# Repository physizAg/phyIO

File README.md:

# What is PhyIO

PhyIO is an IoT development board with ARM cortex-M4 MCU and CC3100 WiFi chipset. It is designed for tinkerers who need high processing and good wireless connectivity for their IoT projects.

Multiple onboard interfaces like I2C, UART, SPI, and RS485 make it easy to experiment with various sensors and actuators. With its extensive features and rugged design, there are endless possibilities.

# Features

1) Onboard Cortex-M4 based STM32 MCU
2) The PhyIO's wireless chip supports 802.11ac/a/b/g/n WiFI
3) Regulates 12V input to 5V and 3.3V
4) Supports transistor-based switching for driving loads
5) Supports I2C, SPI, UART, and RS485 interface
6) Onboard power indicator LED
7) Flexibility to select specific voltage levels amongst multiple voltage levels for interfaces

## Specs

<li>12V input supply</li>
<li>1 MB Flash memory</li>
<li>256Kb RAM</li>
<li>8 I2C ports</li>
<li>4 SPI ports</li>
<li>1 UART port</li>
<li>RS485 port</li>
<li>10 GPIO ports</li>
<li>4 12-bit ADC channels</li>

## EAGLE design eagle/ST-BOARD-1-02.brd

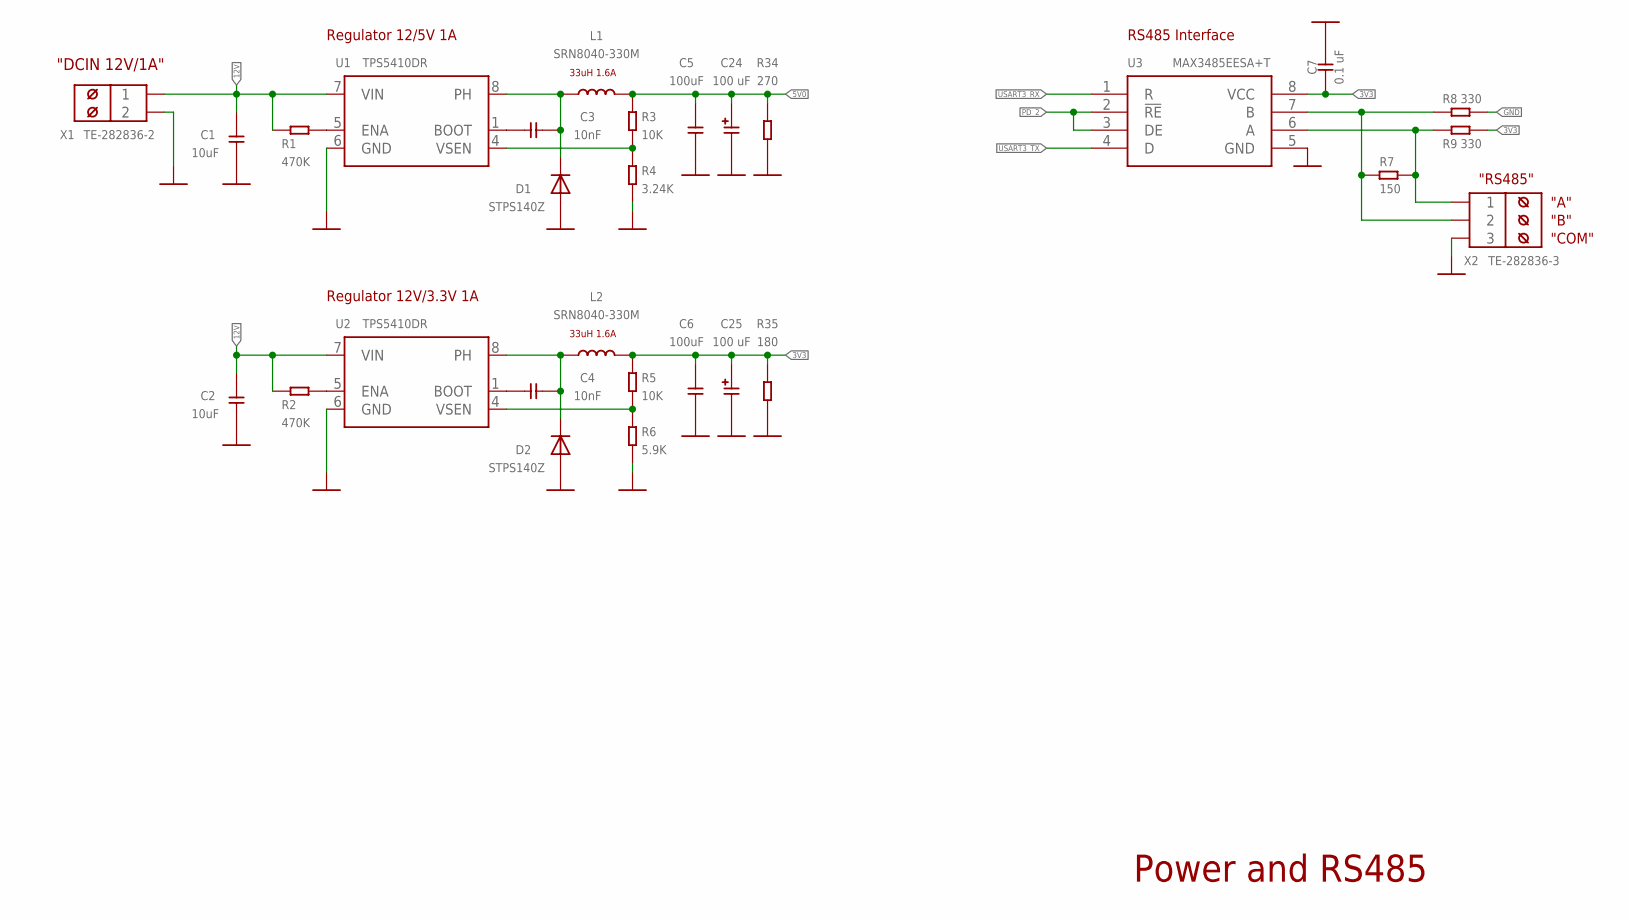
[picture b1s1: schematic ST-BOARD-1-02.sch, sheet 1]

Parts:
C1, C2: 10uF; C1206
C3, C4: 10nF; C0603
C5, C6: 100uF; C1206
C7: 0.1 uF; C0603
C24, C25: 100 uF; CT7343
D1, D2: STPS140Z; SOD-123
L1, L2: SRN8040-330M; SRN8040
R1, R2: 470K; R0603
R3, R5: 10K; R0603
R4: 3.24K; R0603
R6: 5.9K; R0603
R7: 150; R0805
R8, R9: 330; R0603
R34: 270; R1206
R35: 180; R1206
U1, U2: TPS5410DR; SOIC8
U3: MAX3485EESA+T; SOIC8
X1: TE-282836-2; W237-102
X2: TE-282836-3; W237-103

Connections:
3V3: C6.2, C7.1, C25.+, L2.2, R5.2, R9.1, R35.2, U3.8 (VCC); also elsewhere on the board
5V0: C5.2, C24.+, L1.2, R3.2, R34.2; also elsewhere on the board
12V: C1.1, C2.1, R1.2, R2.2, U1.7 (VIN), U2.7 (VIN), X1.1; also elsewhere on the board
A: R7.2, R9.2, U3.6 (A), X2.1
B: R7.1, R8.2, U3.7 (B), X2.2
GND: C1.2, C2.2, C5.1, C6.1, C7.2, C24.-, C25.-, D1.+, D2.+, R4.1, R6.1, R8.1, R34.1, R35.1, U1.6 (GND), U2.6 (GND), U3.5 (GND), X1.2, X2.3; also elsewhere on the board
LM_SW1: C3.2, D1.-, L1.1, U1.8 (PH)
LM_SW3: C4.2, D2.-, L2.1, U2.8 (PH)
unnamed: R3.1, R4.2, U1.4 (VSEN)
unnamed: C3.1, U1.1 (BOOT)
unnamed: R1.1, U1.5 (ENA)
unnamed: R5.1, R6.2, U2.4 (VSEN)
unnamed: C4.1, U2.1 (BOOT)
unnamed: R2.1, U2.5 (ENA)
PD_2: U3.2 (!RE), U3.3 (DE); also elsewhere on the board
USART3_RX: U3.1 (R); also elsewhere on the board
USART3_TX: U3.4 (D); also elsewhere on the board

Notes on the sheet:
"DCIN 12V/1A"
Regulator 12/5V 1A
33uH 1.6A
Regulator 12V/3.3V 1A
RS485 Interface
"RS485"
"A"
"B"
"COM"
Power and RS485

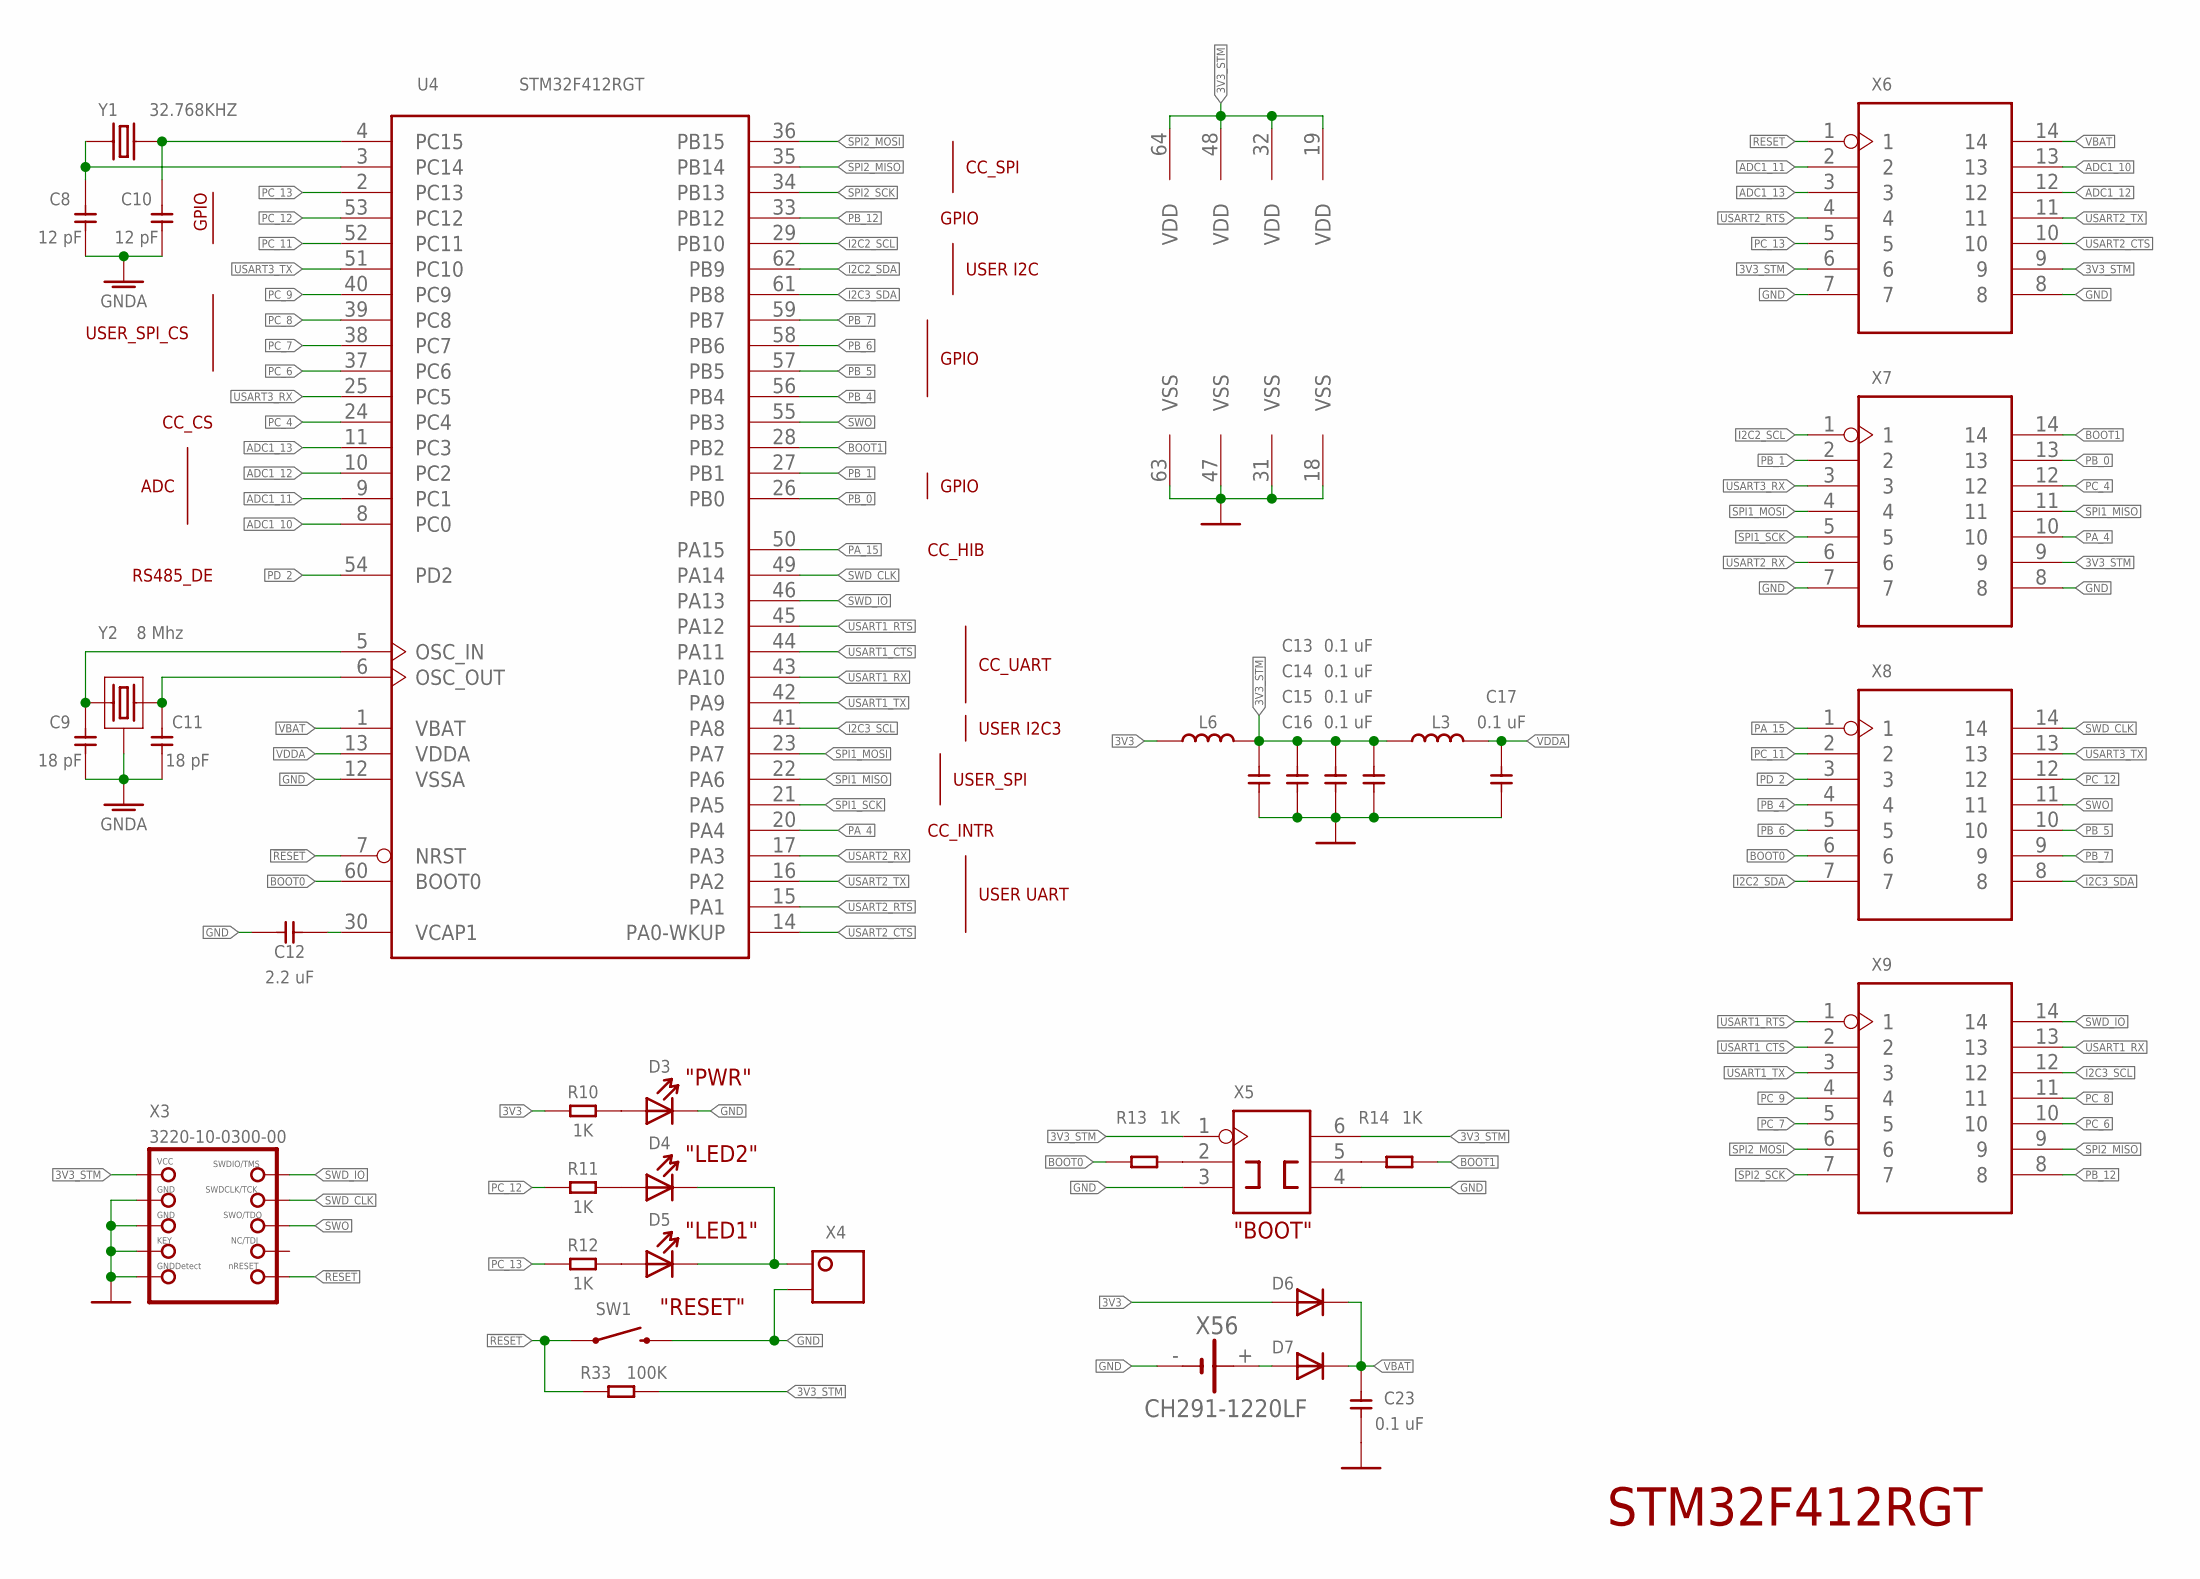
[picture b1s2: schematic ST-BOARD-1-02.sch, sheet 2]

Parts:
C8, C10: 12 pF; C0603
C9, C11: 18 pF; C0603
C12: 2.2 uF; C0603
C13, C14, C15, C16, C17, C23: 0.1 uF; C0603
D3, D4, D5: LED-0603
D6, D7: DIODE_SOD-523; SOD-523
L3, L6: CHIP-INDUCTOR_L0603; L0603
R10, R11, R12, R13, R14: 1K; R0603
R33: 100K; R0603
SW1: TE-1437566-3
U4: STM32F412RGT; LQFP64
X3: 3220-10-0300-00; 2X05_1.27MM_BOX_NOPOSTS
X4: 2p-2.54; H2-2.54
X5: 2x3p-2.54; H2X3-2.54
X6, X7, X8, X9: DIP-HEADER-VERT(2X7P-2.54); H2X7-2.54
X56: CH291-1220LF
Y1: 32.768KHZ; 3.2X1.5; MPN KX-327NHT 32.768 kHz GEYER
Y2: 8 Mhz; IQG5032B

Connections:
3V3: D6.+, L6.1, R10.1; also elsewhere on the board
3V3_STM: C13.1, C14.1, C15.1, C16.1, L3.2, L6.2, R33.1, U4.19 (VDD), U4.32 (VDD), U4.48 (VDD), U4.64 (VDD), X3.1 (VCC), X5.1, X5.6, X6.6, X6.9, X7.9
!RESET: R33.2, SW1.P$1 (1), U4.7 (NRST), X3.10 (NRESET), X6.1
ADC1_10: U4.8 (PC0), X6.13; also elsewhere on the board
ADC1_11: U4.9 (PC1), X6.2; also elsewhere on the board
ADC1_12: U4.10 (PC2), X6.12; also elsewhere on the board
ADC1_13: U4.11 (PC3), X6.3; also elsewhere on the board
BOOT0: R13.1, U4.60 (BOOT0), X8.6
BOOT1: R14.1, U4.28 (PB2), X7.14
GND: C12.2, C13.2, C14.2, C15.2, C16.2, C17.2, C23.2, D3.-, SW1.P$2 (2), U4.12 (VSSA), U4.18 (VSS), U4.31 (VSS), U4.47 (VSS), U4.63 (VSS), X3.3 (GND), X3.5 (GND), X3.7 (KEY), X3.9 (GNDDETECT), X4.2, X5.3, X5.4, X6.7, X6.8, X7.7, X7.8, X56.-; also elsewhere on the board
GNDA: C8.1, C9.1, C10.1, C11.1, Y2.2 (GND), Y2.4 (GND)
I2C2_SCL: U4.29 (PB10), X7.1; also elsewhere on the board
I2C2_SDA: U4.62 (PB9), X8.7; also elsewhere on the board
I2C3_SCL: U4.41 (PA8), X9.12; also elsewhere on the board
I2C3_SDA: U4.61 (PB8), X8.8; also elsewhere on the board
unnamed: C10.2, U4.4 (PC15), Y1.2
unnamed: C8.2, U4.3 (PC14), Y1.1
unnamed: C12.1, U4.30 (VCAP1)
unnamed: C11.2, U4.6 (OSC_OUT), Y2.3 (2)
unnamed: C9.2, U4.5 (OSC_IN), Y2.1
unnamed: D3.+, R10.2
unnamed: D4.+, R11.2
unnamed: D5.+, R12.2
unnamed: D7.+, X56.+
unnamed: R14.2, X5.5
unnamed: R13.2, X5.2
unnamed: D4.-, D5.-, X4.1
PA_4: U4.20 (PA4), X7.10; also elsewhere on the board
PA_15: U4.50 (PA15), X8.1; also elsewhere on the board
PB_0: U4.26 (PB0), X7.13; also elsewhere on the board
PB_1: U4.27 (PB1), X7.2; also elsewhere on the board
PB_4: U4.56 (PB4), X8.4; also elsewhere on the board
PB_5: U4.57 (PB5), X8.10; also elsewhere on the board
PB_6: U4.58 (PB6), X8.5; also elsewhere on the board
PB_7: U4.59 (PB7), X8.9; also elsewhere on the board
PB_12: U4.33 (PB12), X9.8; also elsewhere on the board
PC_4: U4.24 (PC4), X7.12; also elsewhere on the board
PC_6: U4.37 (PC6), X9.10; also elsewhere on the board
PC_7: U4.38 (PC7), X9.5; also elsewhere on the board
PC_8: U4.39 (PC8), X9.11; also elsewhere on the board
PC_9: U4.40 (PC9), X9.4; also elsewhere on the board
PC_11: U4.52 (PC11), X8.2; also elsewhere on the board
PC_12: R11.1, U4.53 (PC12), X8.12; also elsewhere on the board
PC_13: R12.1, U4.2 (PC13), X6.5; also elsewhere on the board
PD_2: U4.54 (PD2), X8.3; also elsewhere on the board
SPI1_MISO: U4.22 (PA6), X7.11; also elsewhere on the board
SPI1_MOSI: U4.23 (PA7), X7.4; also elsewhere on the board
SPI1_SCK: U4.21 (PA5), X7.5; also elsewhere on the board
SPI2_MISO: U4.35 (PB14), X9.9; also elsewhere on the board
SPI2_MOSI: U4.36 (PB15), X9.6; also elsewhere on the board
SPI2_SCK: U4.34 (PB13), X9.7; also elsewhere on the board
SWD_CLK: U4.49 (PA14), X3.4 (SWDCLK), X8.14
SWD_IO: U4.46 (PA13), X3.2 (SWDIO), X9.14
SWO: U4.55 (PB3), X3.6 (SWO), X8.11
USART1_CTS: U4.44 (PA11), X9.2; also elsewhere on the board
USART1_RTS: U4.45 (PA12), X9.1; also elsewhere on the board
USART1_RX: U4.43 (PA10), X9.13; also elsewhere on the board
USART1_TX: U4.42 (PA9), X9.3; also elsewhere on the board
USART2_CTS: U4.14 (PA0-WKUP), X6.10; also elsewhere on the board
USART2_RTS: U4.15 (PA1), X6.4; also elsewhere on the board
USART2_RX: U4.17 (PA3), X7.6; also elsewhere on the board
USART2_TX: U4.16 (PA2), X6.11; also elsewhere on the board
USART3_RX: U4.25 (PC5), X7.3; also elsewhere on the board
USART3_TX: U4.51 (PC10), X8.13; also elsewhere on the board
VBAT: C23.1, D6.-, D7.-, U4.1 (VBAT), X6.14
VDDA: C17.1, L3.1, U4.13 (VDDA)

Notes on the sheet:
STM32F412RGT
"PWR"
"LED2"
"LED1"
"RESET"
USER UART
CC_UART
USER_SPI
USER I2C
USER I2C3
CC_SPI
"BOOT"
RS485_DE
ADC
GPIO
USER_SPI_CS
CC_INTR
CC_HIB
CC_CS

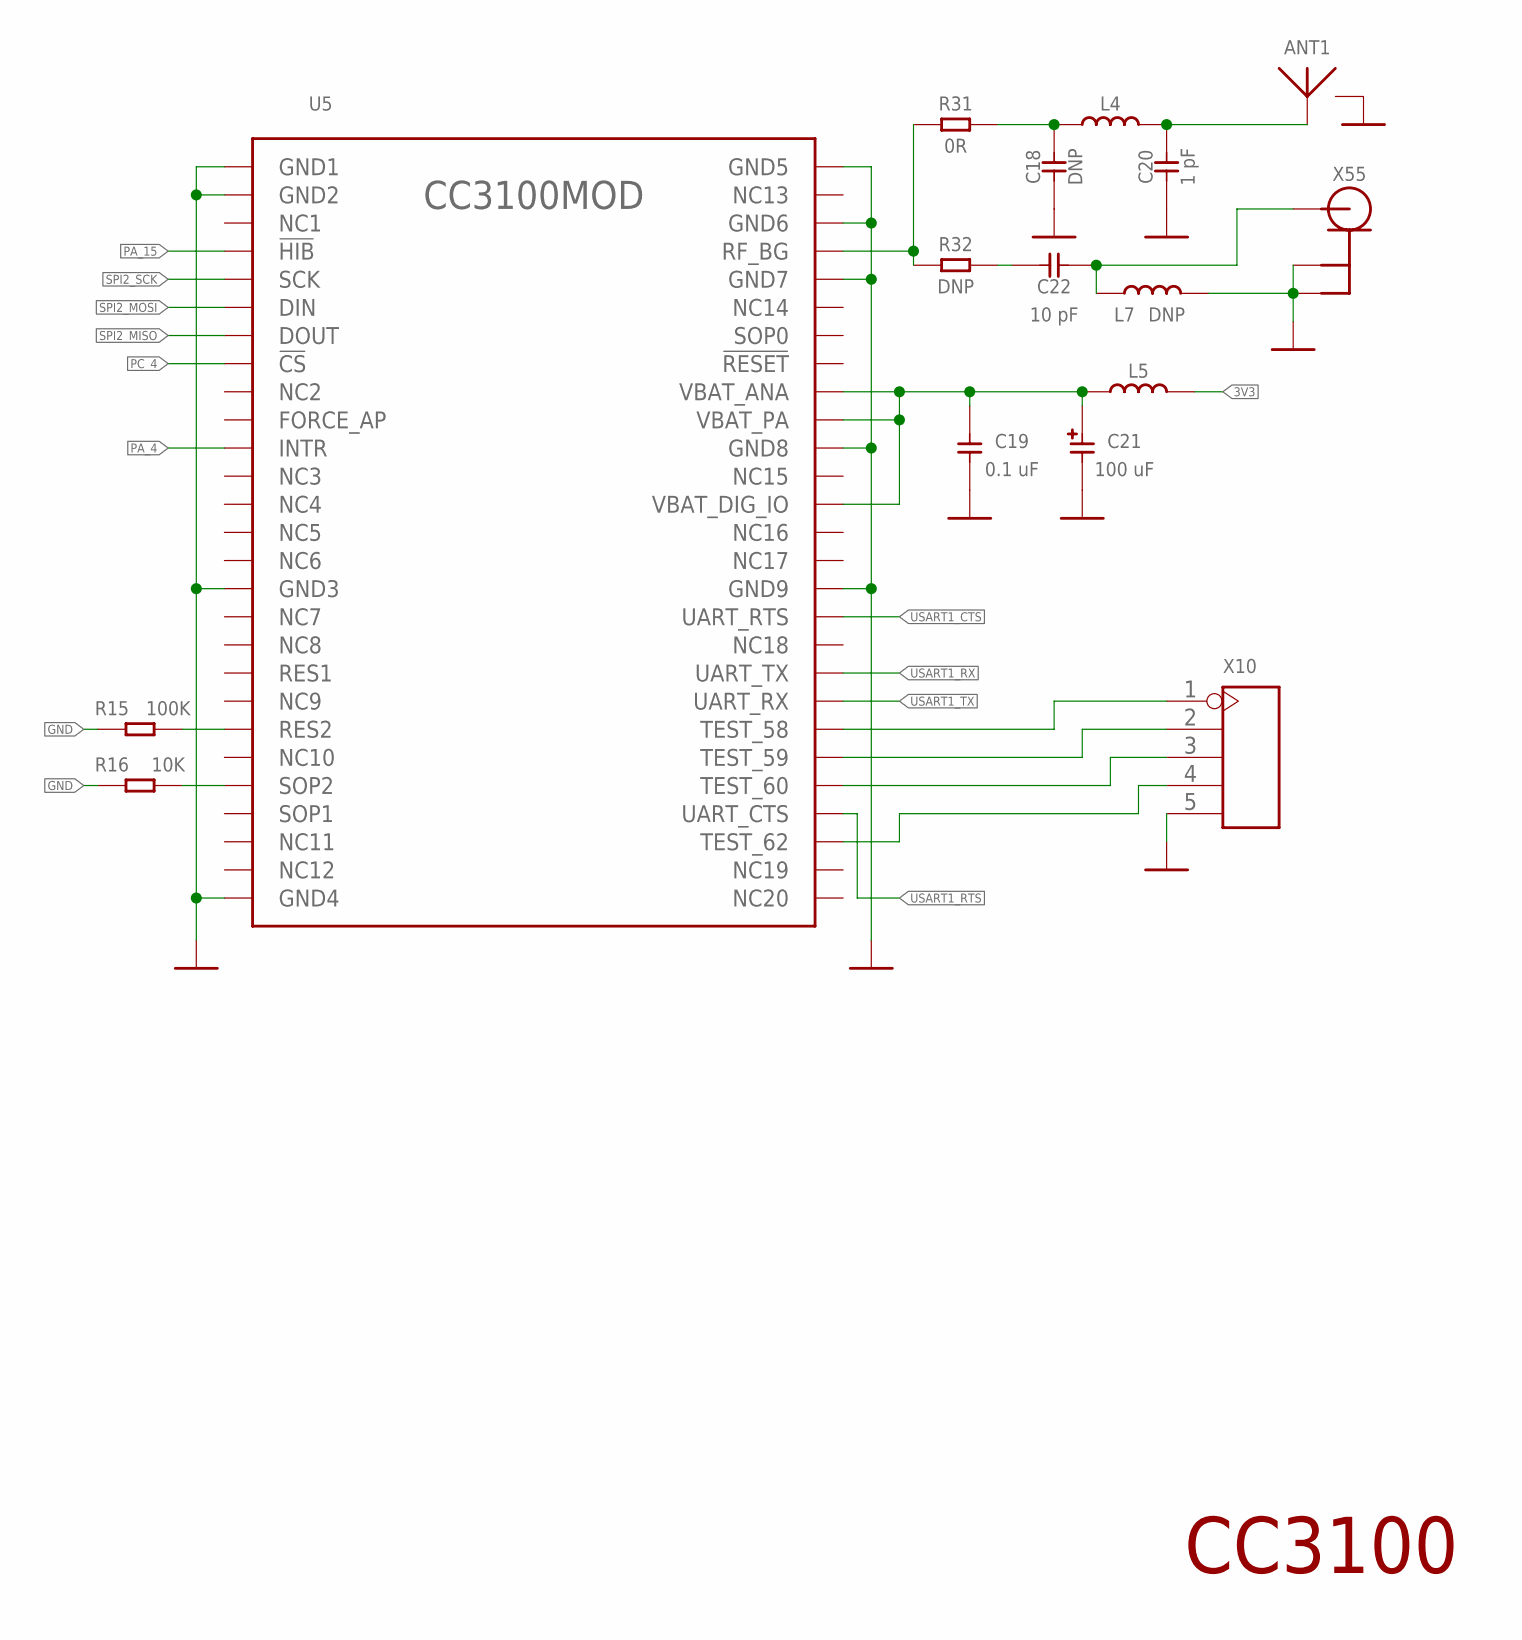
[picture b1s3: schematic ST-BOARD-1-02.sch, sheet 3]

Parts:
ANT1: AH316M245001-T; AH316M
C18: DNP; C0402
C19: 0.1 uF; C0603
C20: 1 pF; C0402
C21: 100 uF; CT3528
C22: 10 pF; C0402
L4: CHIP-INDUCTOR_L0402; L0402
L5: CHIP-INDUCTOR_L0603; L0603
L7: DNP; L0402
R15: 100K; R0603
R16: 10K; R0603
R31: 0R; R0402
R32: DNP; R0402
U5: CC3100MOD
X10: 2p-2.54; H5-2.54
X55: UFL3; U-FL3P-SMD-2.6X2.6X1.0MM

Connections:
3V3: L5.2; also elsewhere on the board
GND: ANT1.P$2 (GND), C18.1, C19.2, C20.1, C21.-, L7.2, R15.1, R16.1, U5.P1 (GND1), U5.P2 (GND2), U5.P16 (GND3), U5.P27 (GND4), U5.P28 (GND5), U5.P30 (GND6), U5.P32 (GND7), U5.P38 (GND8), U5.P43 (GND9), U5.P55 (GND1), U5.P56 (GND1), U5.P57 (GND1), U5.P58 (GND1), U5.P59 (GND1), U5.P60 (GND1), U5.P61 (GND1), U5.P62 (GND1), U5.P63 (GND1), X10.5, X55.GND1 (GND), X55.GND2 (GND1); also elsewhere on the board
unnamed: R15.2, U5.P21 (RES2)
unnamed: R16.2, U5.P23 (SOP2)
unnamed: R31.1, R32.1, U5.P31 (RF_BG)
unnamed: ANT1.P$1 (ANT), C20.2, L4.2
unnamed: C19.1, C21.+, L5.1, U5.P36 (VBAT_ANA), U5.P37 (VBAT_PA), U5.P40 (VBAT_DIG_IO)
unnamed: C18.2, L4.1, R31.2
unnamed: C22.2, R32.2
unnamed: C22.1, L7.1, X55.D (ANT)
PA_4: U5.P11 (INTR); also elsewhere on the board
PA_15: U5.P4 (!HIB); also elsewhere on the board
PC_4: U5.P8 (!CS); also elsewhere on the board
SPI2_MISO: U5.P7 (DOUT); also elsewhere on the board
SPI2_MOSI: U5.P6 (DIN); also elsewhere on the board
SPI2_SCK: U5.P5 (SCK); also elsewhere on the board
TEST_58: U5.P48 (TEST_58), X10.1
TEST_59: U5.P49 (TEST_59), X10.2
TEST_60: U5.P50 (TEST_60), X10.3
TEST_62: U5.P52 (TEST_62), X10.4
USART1_CTS: U5.P44 (UART_RTS); also elsewhere on the board
USART1_RTS: U5.P51 (UART_CTS); also elsewhere on the board
USART1_RX: U5.P46 (UART_TX); also elsewhere on the board
USART1_TX: U5.P47 (UART_RX); also elsewhere on the board

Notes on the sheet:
CC3100

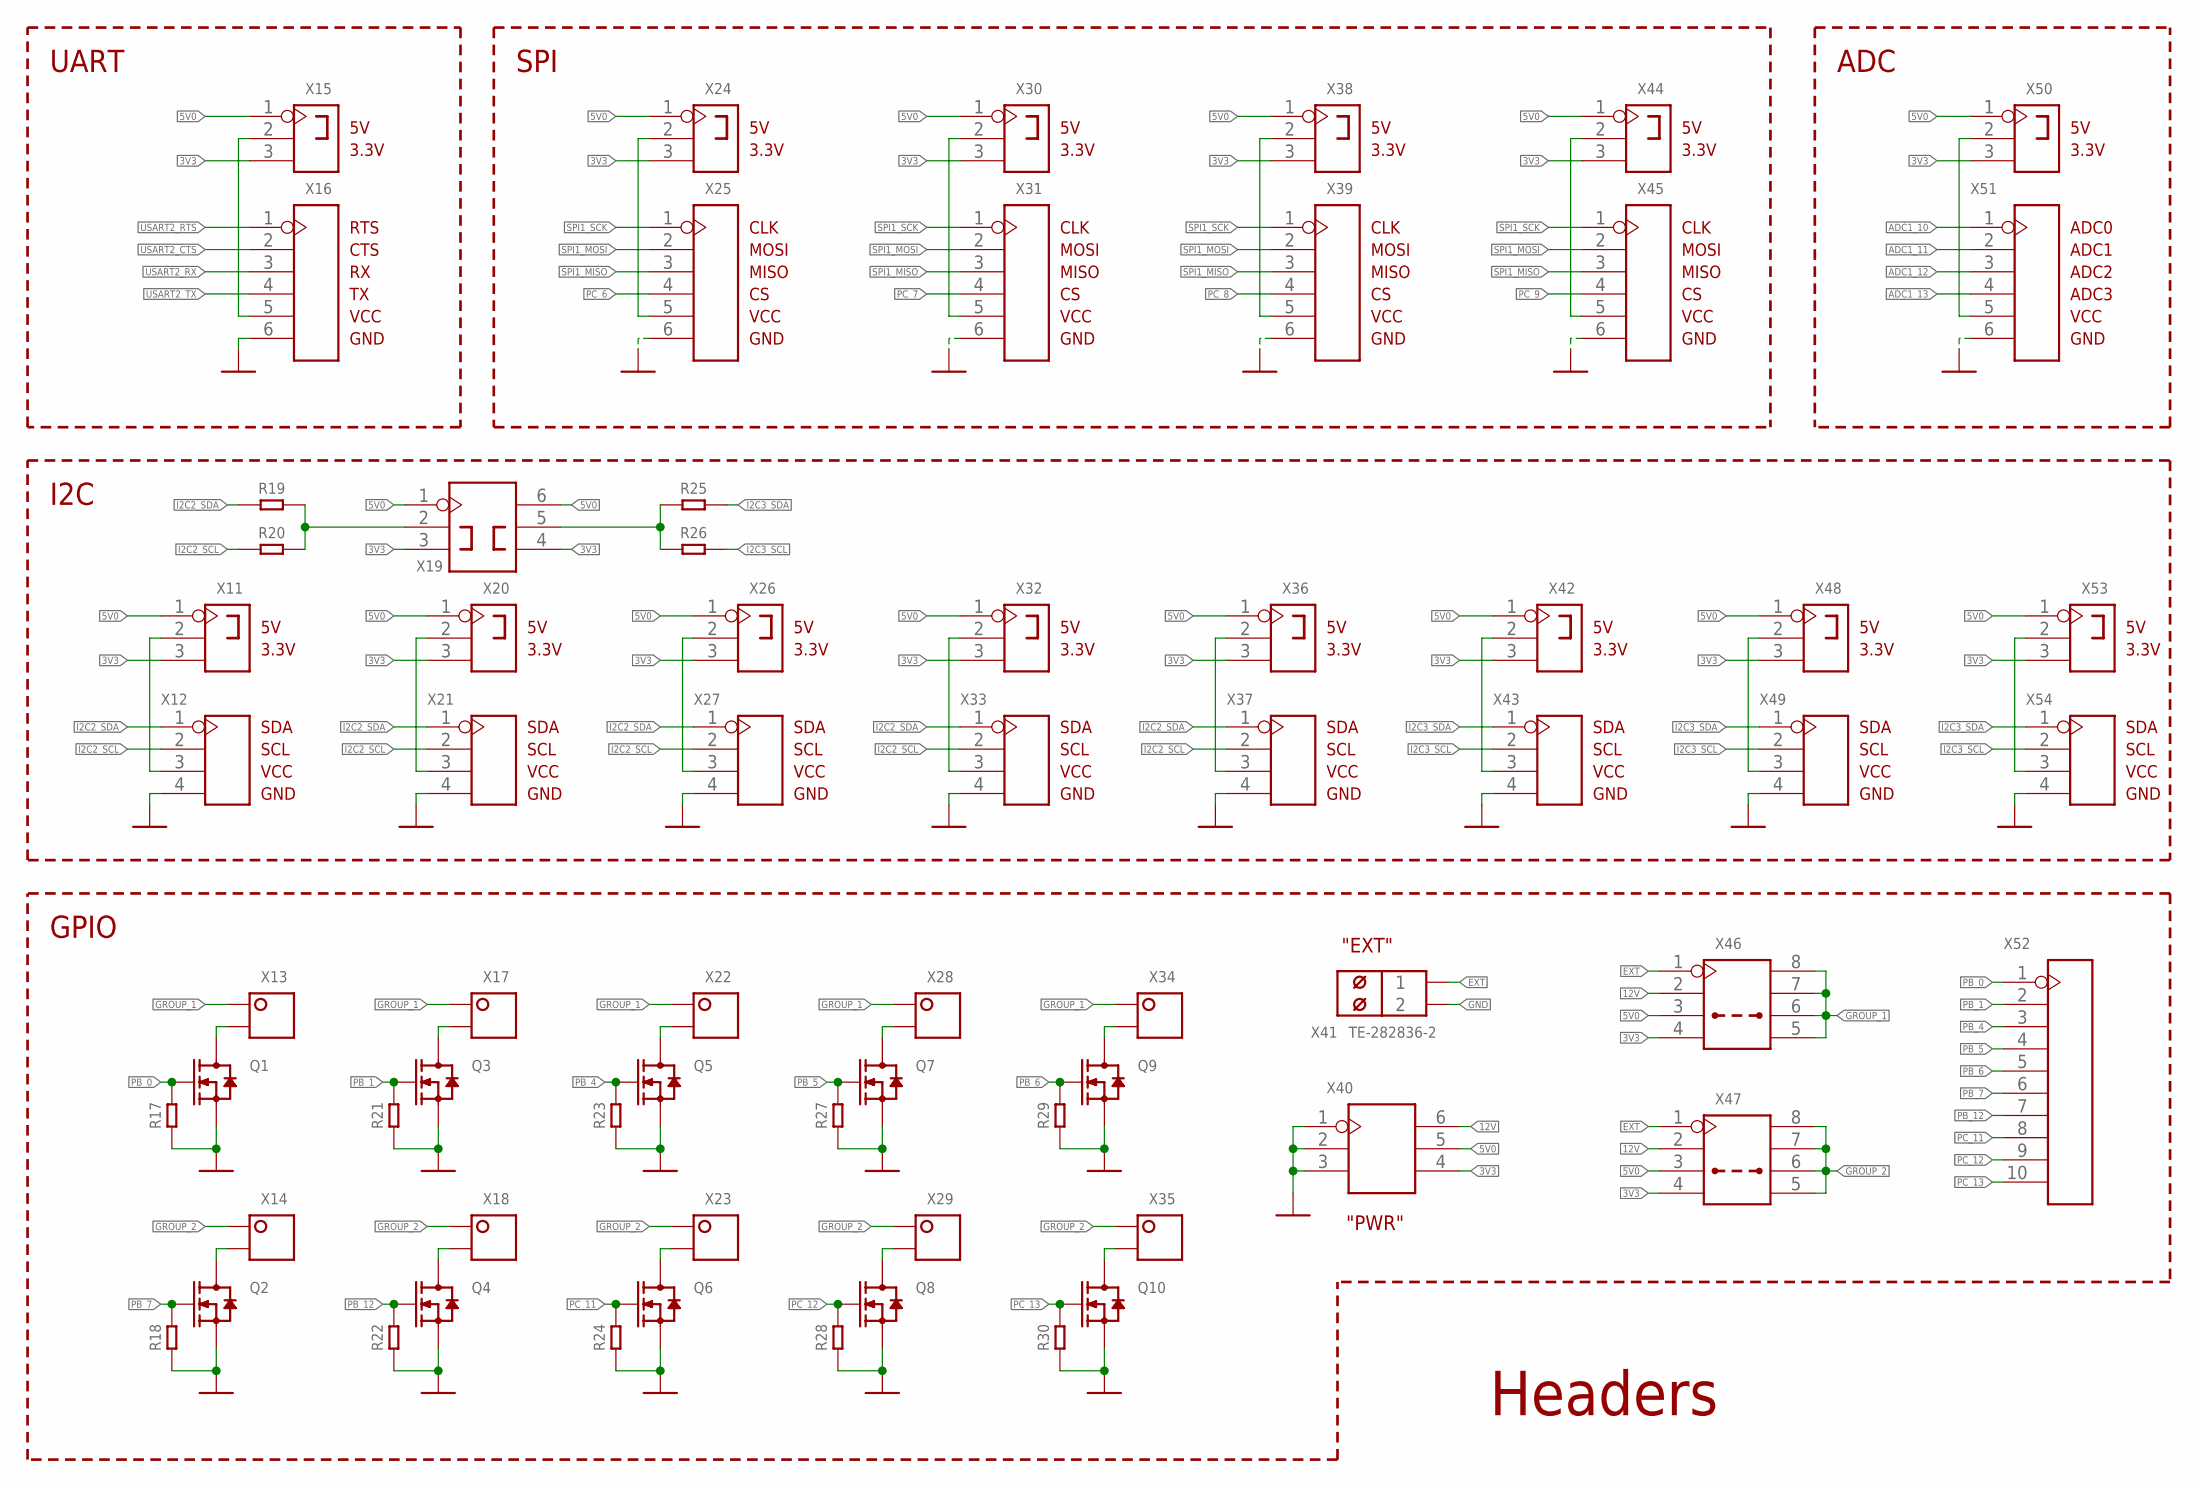
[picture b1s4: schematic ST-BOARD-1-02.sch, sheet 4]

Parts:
Q1, Q2, Q3, Q4, Q5, Q6, Q7, Q8, Q9, Q10: MOSFET-N-(SOT-23); SOT-23
R17, R18, R19, R20, R21, R22, R23, R24, R25, R26, R27, R28, R29, R30: CHIP-RESISTOR-0603; R0603
X11, X15, X20, X24, X26, X30, X32, X36, X38, X42, X44, X48, X50, X53: 3p-2.54; H3-2.54
X12, X21, X27, X33, X37, X43, X49, X54: DIP-HEADER-VERT(4P-2.54)_WF; 22-23-2041
X13, X14, X17, X18, X22, X23, X28, X29, X34, X35: 2p-2.54; 22-23-2021
X16, X25, X31, X39, X45: DIP-HEADER-VERT(6P-2.54)_WF; 22-23-2061
X19, X40: 2x3p-2.54; H2X3-2.54
X41: TE-282836-2; W237-102
X46, X47: 2x4p-2.54; H2X4-2.54
X51: DIP-HEADER-VERT(6P-2.54); H6-2.54
X52: DIP-HEADER-VERT(10P-2.54); H10-2.54

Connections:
3V3: X11.3, X15.3, X19.3, X19.4, X20.3, X24.3, X26.3, X30.3, X32.3, X36.3, X38.3, X40.4, X42.3, X44.3, X46.4, X47.4, X48.3, X50.3, X53.3; also elsewhere on the board
5V0: X11.1, X15.1, X19.1, X19.6, X20.1, X24.1, X26.1, X30.1, X32.1, X36.1, X38.1, X40.5, X42.1, X44.1, X46.3, X47.3, X48.1, X50.1, X53.1; also elsewhere on the board
12V: X40.6, X46.2, X47.2; also elsewhere on the board
ADC1_10: X51.1; also elsewhere on the board
ADC1_11: X51.2; also elsewhere on the board
ADC1_12: X51.3; also elsewhere on the board
ADC1_13: X51.4; also elsewhere on the board
EXT: X41.1, X46.1, X47.1
GND: Q1.2 (S), Q2.2 (S), Q3.2 (S), Q4.2 (S), Q5.2 (S), Q6.2 (S), Q7.2 (S), Q8.2 (S), Q9.2 (S), Q10.2 (S), R17.1, R18.1, R21.1, R22.1, R23.1, R24.1, R27.1, R28.1, R29.1, R30.1, X12.4, X16.6, X21.4, X25.6, X27.4, X31.6, X33.4, X37.4, X39.6, X40.1, X40.2, X40.3, X41.2, X43.4, X45.6, X49.4, X51.6, X54.4; also elsewhere on the board
GROUP_1: X13.1, X17.1, X22.1, X28.1, X34.1, X46.5, X46.6, X46.7, X46.8
GROUP_2: X14.1, X18.1, X23.1, X29.1, X35.1, X47.5, X47.6, X47.7, X47.8
I2C2_SCL: R20.1, X12.2, X21.2, X27.2, X33.2, X37.2; also elsewhere on the board
I2C2_SDA: R19.1, X12.1, X21.1, X27.1, X33.1, X37.1; also elsewhere on the board
I2C3_SCL: R26.1, X43.2, X49.2, X54.2; also elsewhere on the board
I2C3_SDA: R25.1, X43.1, X49.1, X54.1; also elsewhere on the board
unnamed: R19.2, R20.2, X19.2
unnamed: X11.2, X12.3
unnamed: X20.2, X21.3
unnamed: X15.2, X16.5
unnamed: X26.2, X27.3
unnamed: Q1.3 (D), X13.2
unnamed: Q3.3 (D), X17.2
unnamed: X32.2, X33.3
unnamed: X36.2, X37.3
unnamed: X42.2, X43.3
unnamed: X48.2, X49.3
unnamed: X53.2, X54.3
unnamed: X24.2, X25.5
unnamed: X30.2, X31.5
unnamed: X38.2, X39.5
unnamed: X44.2, X45.5
unnamed: X50.2, X51.5
unnamed: Q5.3 (D), X22.2
unnamed: Q7.3 (D), X28.2
unnamed: Q9.3 (D), X34.2
unnamed: Q2.3 (D), X14.2
unnamed: Q4.3 (D), X18.2
unnamed: Q6.3 (D), X23.2
unnamed: Q8.3 (D), X29.2
unnamed: Q10.3 (D), X35.2
unnamed: R25.2, R26.2, X19.5
PB_0: Q1.1 (G), R17.2, X52.1; also elsewhere on the board
PB_1: Q3.1 (G), R21.2, X52.2; also elsewhere on the board
PB_4: Q5.1 (G), R23.2, X52.3; also elsewhere on the board
PB_5: Q7.1 (G), R27.2, X52.4; also elsewhere on the board
PB_6: Q9.1 (G), R29.2, X52.5; also elsewhere on the board
PB_7: Q2.1 (G), R18.2, X52.6; also elsewhere on the board
PB_12: Q4.1 (G), R22.2, X52.7; also elsewhere on the board
PC_6: X25.4; also elsewhere on the board
PC_7: X31.4; also elsewhere on the board
PC_8: X39.4; also elsewhere on the board
PC_9: X45.4; also elsewhere on the board
PC_11: Q6.1 (G), R24.2, X52.8; also elsewhere on the board
PC_12: Q8.1 (G), R28.2, X52.9; also elsewhere on the board
PC_13: Q10.1 (G), R30.2, X52.10; also elsewhere on the board
SPI1_MISO: X25.3, X31.3, X39.3, X45.3; also elsewhere on the board
SPI1_MOSI: X25.2, X31.2, X39.2, X45.2; also elsewhere on the board
SPI1_SCK: X25.1, X31.1, X39.1, X45.1; also elsewhere on the board
USART2_CTS: X16.2; also elsewhere on the board
USART2_RTS: X16.1; also elsewhere on the board
USART2_RX: X16.3; also elsewhere on the board
USART2_TX: X16.4; also elsewhere on the board

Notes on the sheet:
3.3V
VCC
GND
UART
SDA
SCL
CLK
MOSI
MISO
ADC0
ADC1
ADC2
ADC3
SPI
GPIO
I2C
ADC
Headers
CTS
RTS
"EXT"
"PWR"

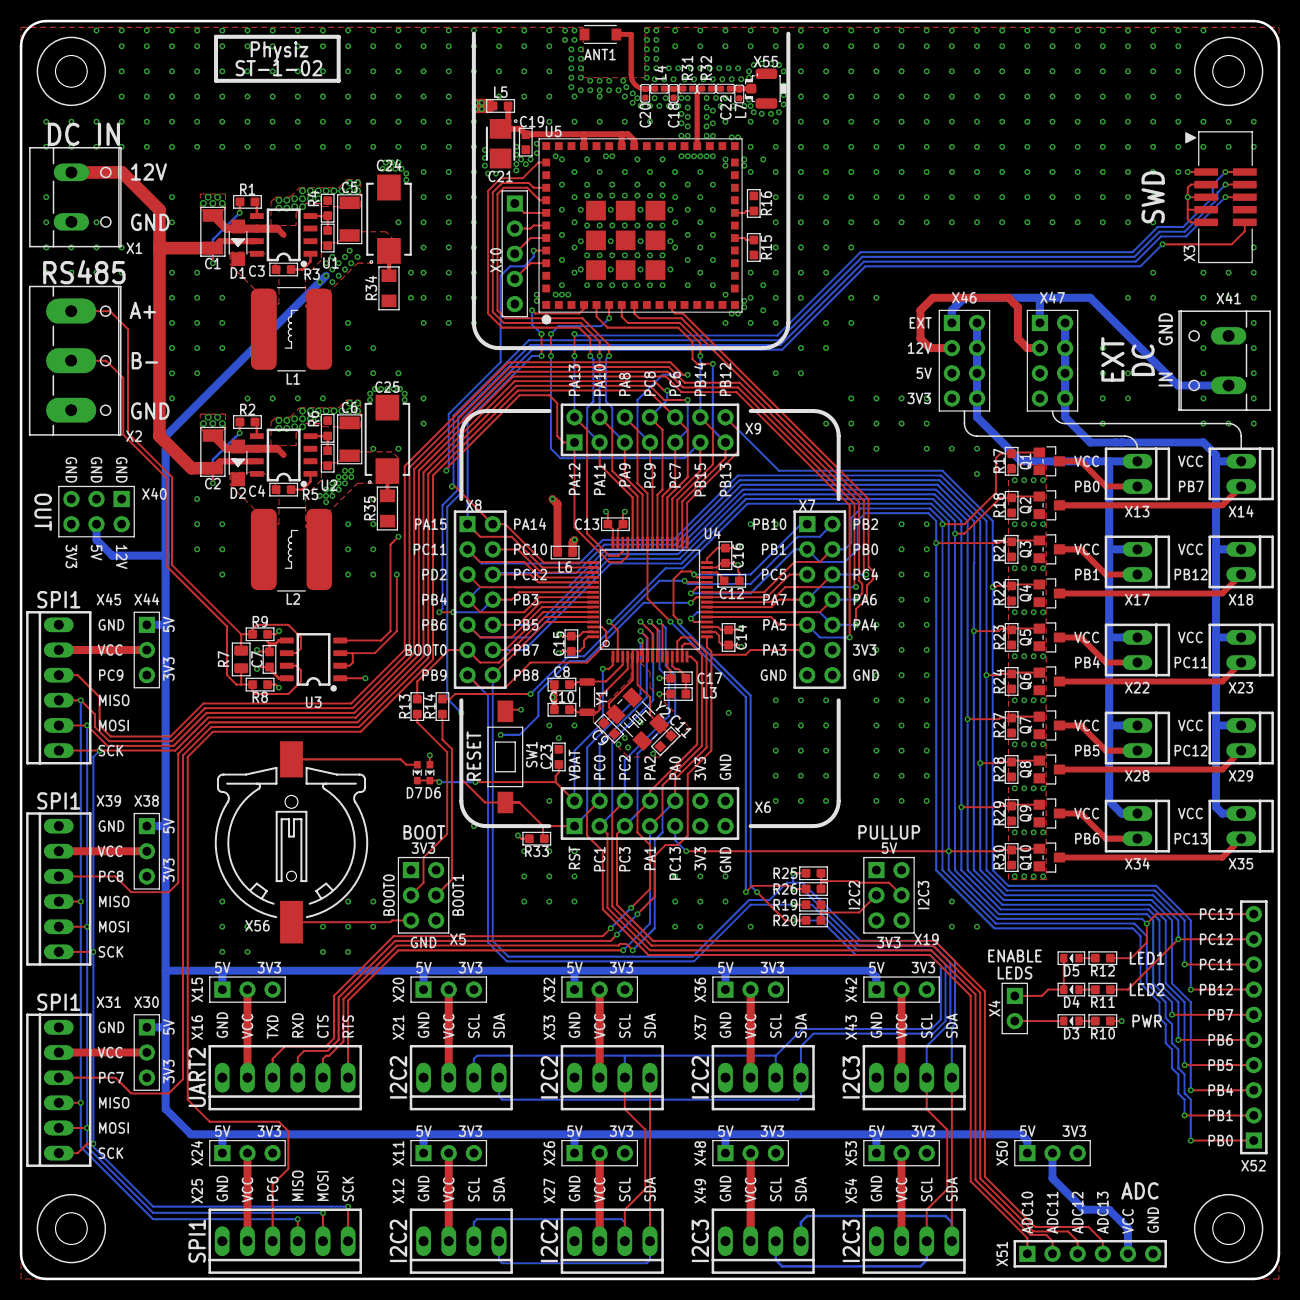
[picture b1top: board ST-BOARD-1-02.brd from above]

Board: 4 copper layers, 127.0 x 127.0 mm, 155 parts (0 on the bottom side), 119 nets.

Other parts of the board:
DRILEGEND: DRILEGEND
U$1, U$2, U$3, U$4: 3,2
U$5: A4P-LOC

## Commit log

2020-06-22 Initial Commit
    Uploaded all design files
2020-06-23 Readme Updated
